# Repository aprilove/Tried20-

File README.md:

# Tried20%

An attempt at creating a 20% mechanical keyboard without an Arduino. 

- [ ] Reroute to remove the amount of vias
- [x] Add circuit protection

A follow up will probably be made to improve the readibility by implementing an Arduino Pro Micro.

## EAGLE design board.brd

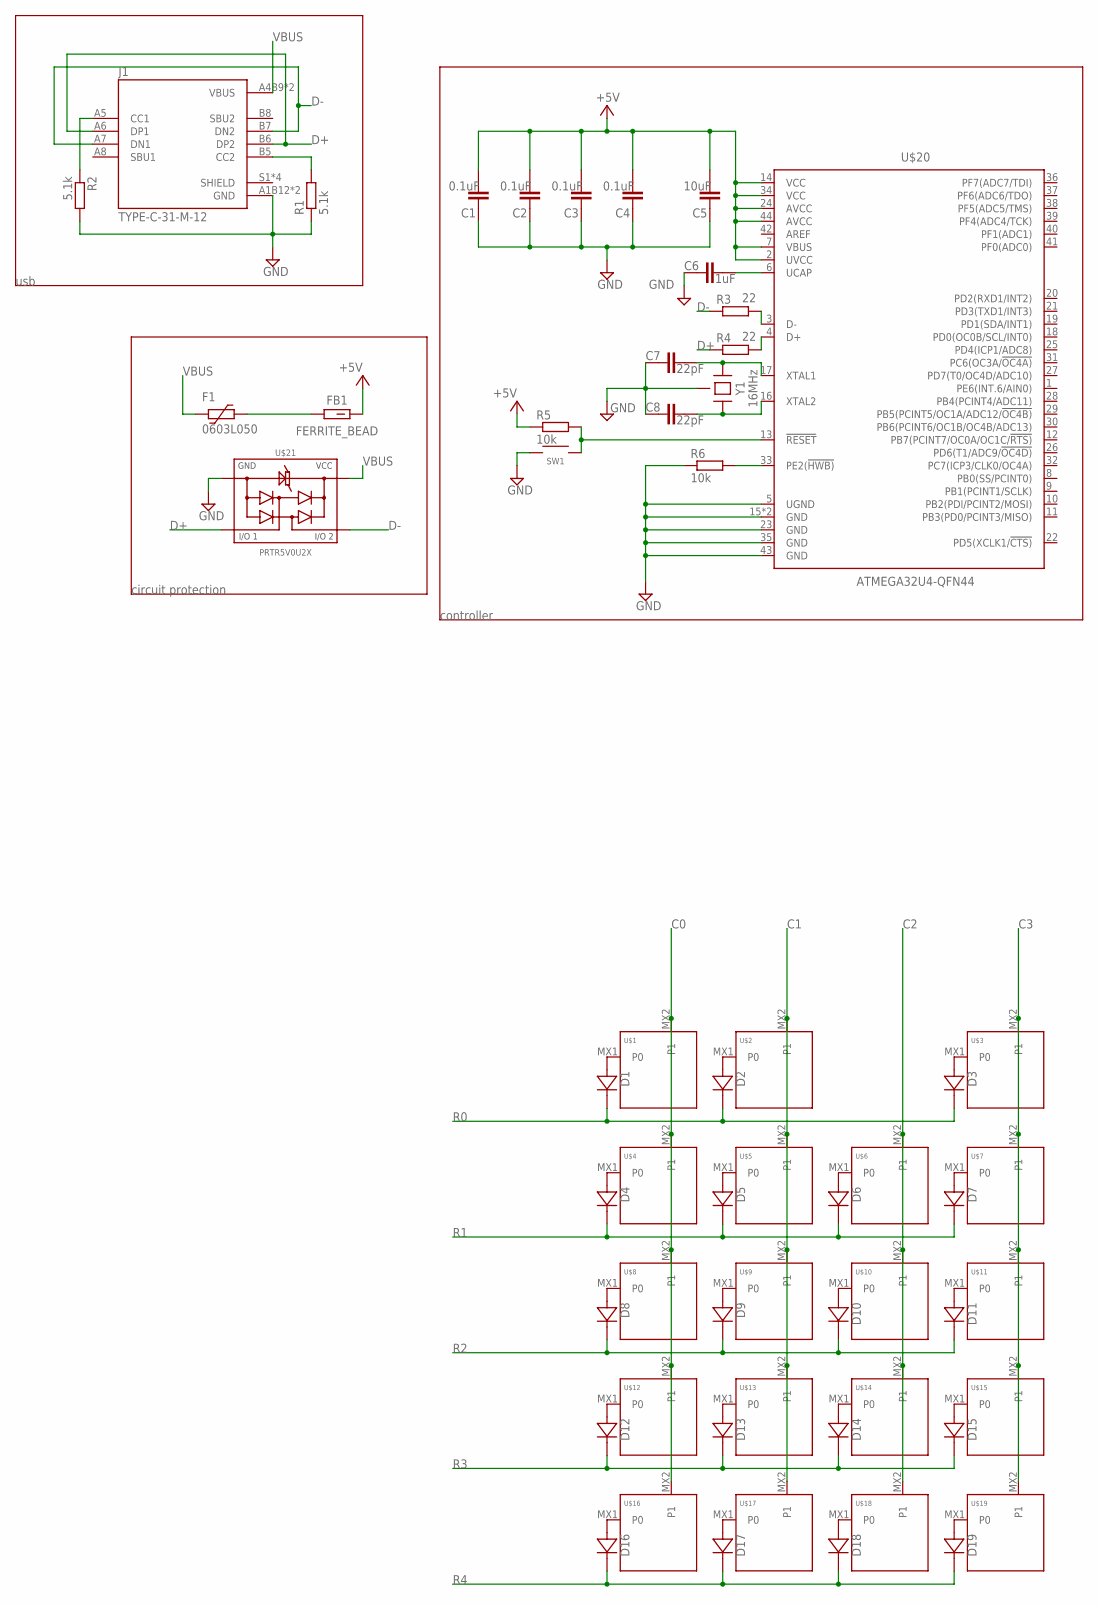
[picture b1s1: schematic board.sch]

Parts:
C1, C2, C3, C4: 0.1uF; C0603
C5: 10uF; C0603
C6: 1uF; C0603
C7, C8: 22pF; C0603
D1, D2, D3, D4, D5, D6, D7, D8, D9, D10, D11, D12, D13, D14, D15, D16, D17, D18, D19: DIODE-SOD-123; SOD-123
F1: 0603L050; 0603L
FB1: FERRITE_BEAD; BEADC1608X95N
J1: TYPE-C-31-M-12; HRO_TYPE-C-31-M-12
R1, R2: 5.1k; R0603
R3, R4: 22; R0603
R5, R6: 10k; R0603
SW1: SWITCH-SMD-EVP-BB2A9B00
U$1, U$3, U$4, U$5, U$6, U$7, U$8, U$9, U$10, U$11, U$12, U$13, U$14, U$15, U$16, U$17, U$18, U$19: KEYSWITCH-PLAIN-MX-1U; MX-1U
U$2: KEYSWITCH-PLAIN-MX-2U-FLIPPED; MX-2U-FLIPPED
U$20: ATMEGA32U4-QFN44; QFN-44
U$21: PRTR5V0U2X
Y1: 16MHz; CRYSTAL-3.2X2.5

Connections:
C0: U$1.MX2 (P1), U$4.MX2 (P1), U$8.MX2 (P1), U$12.MX2 (P1), U$16.MX2 (P1)
C1: U$2.MX2 (P1), U$5.MX2 (P1), U$9.MX2 (P1), U$13.MX2 (P1), U$17.MX2 (P1)
C2: U$6.MX2 (P1), U$10.MX2 (P1), U$14.MX2 (P1), U$18.MX2 (P1)
C3: U$3.MX2 (P1), U$7.MX2 (P1), U$11.MX2 (P1), U$15.MX2 (P1), U$19.MX2 (P1)
D+: J1.A6 (DP1), J1.B6 (DP2), R4.1, U$21.2
D-: J1.A7 (DN1), J1.B7 (DN2), R3.1, U$21.3
GND: C1.1, C2.1, C3.1, C4.1, C5.1, C6.1, C7.1, C8.1, J1.A1B12 (GND), J1.B1A12 (GND), R1.1, R2.2, R6.1, SW1.A@1 (1), SW1.A@2 (1), U$20.5 (UGND), U$20.15 (GND), U$20.23 (GND), U$20.35 (GND), U$20.43 (GND), U$20.TAB (GND), U$21.1, Y1.2 (GND), Y1.4 (GND)
unnamed: D1.A, U$1.MX1 (P0)
unnamed: D2.A, U$2.MX1 (P0)
unnamed: D3.A, U$3.MX1 (P0)
unnamed: D4.A, U$4.MX1 (P0)
unnamed: D5.A, U$5.MX1 (P0)
unnamed: D6.A, U$6.MX1 (P0)
unnamed: D7.A, U$7.MX1 (P0)
unnamed: D8.A, U$8.MX1 (P0)
unnamed: D9.A, U$9.MX1 (P0)
unnamed: D10.A, U$10.MX1 (P0)
unnamed: D11.A, U$11.MX1 (P0)
unnamed: D12.A, U$12.MX1 (P0)
unnamed: D13.A, U$13.MX1 (P0)
unnamed: D14.A, U$14.MX1 (P0)
unnamed: D15.A, U$15.MX1 (P0)
unnamed: D16.A, U$16.MX1 (P0)
unnamed: D17.A, U$17.MX1 (P0)
unnamed: D18.A, U$18.MX1 (P0)
unnamed: D19.A, U$19.MX1 (P0)
unnamed: J1.A5 (CC1), R2.1
unnamed: C6.2, U$20.6 (UCAP)
unnamed: C7.2, U$20.17 (XTAL1), Y1.1
unnamed: J1.B5 (CC2), R1.2
unnamed: R3.2, U$20.3 (D-)
unnamed: R4.2, U$20.4 (D+)
unnamed: C8.2, U$20.16 (XTAL2), Y1.3 (2)
unnamed: R5.2, SW1.B@3 (2), SW1.B@4 (2), U$20.13 (!RESET)
unnamed: R6.2, U$20.33 (PE2(!HWB))
unnamed: F1.1, FB1.1
R0: D1.C, D2.C, D3.C
R1: D4.C, D5.C, D6.C, D7.C
R2: D8.C, D9.C, D10.C, D11.C
R3: D12.C, D13.C, D14.C, D15.C
R4: D16.C, D17.C, D18.C, D19.C
VBUS: F1.2, J1.A4B9 (VBUS), J1.B4A9 (VBUS), U$21.4
VCC: C1.2, C2.2, C3.2, C4.2, C5.2, FB1.2, R5.1, U$20.2 (UVCC), U$20.7 (VBUS), U$20.14 (VCC), U$20.24 (AVCC), U$20.34 (VCC), U$20.44 (AVCC)

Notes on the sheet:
controller
usb
circuit protection

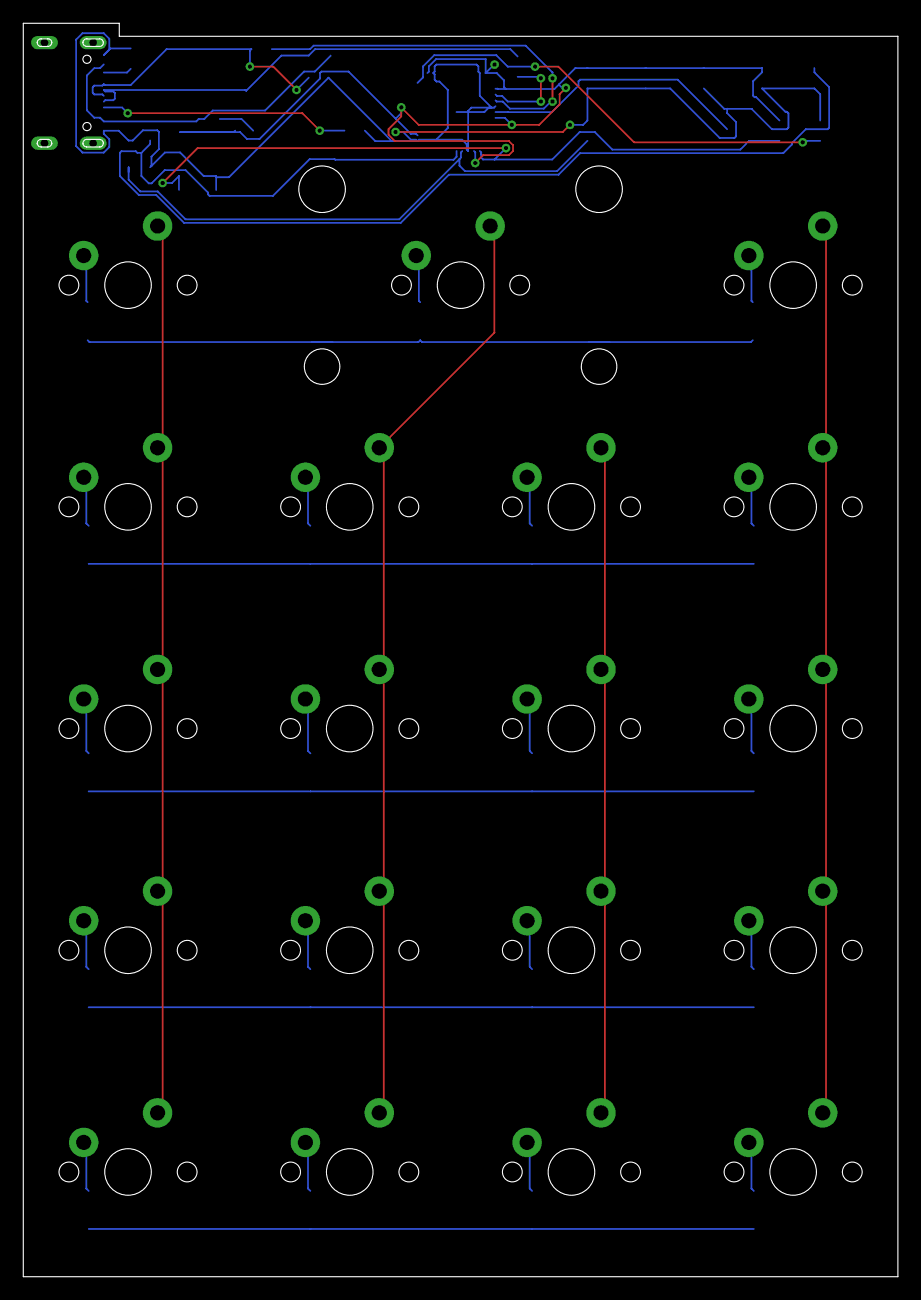
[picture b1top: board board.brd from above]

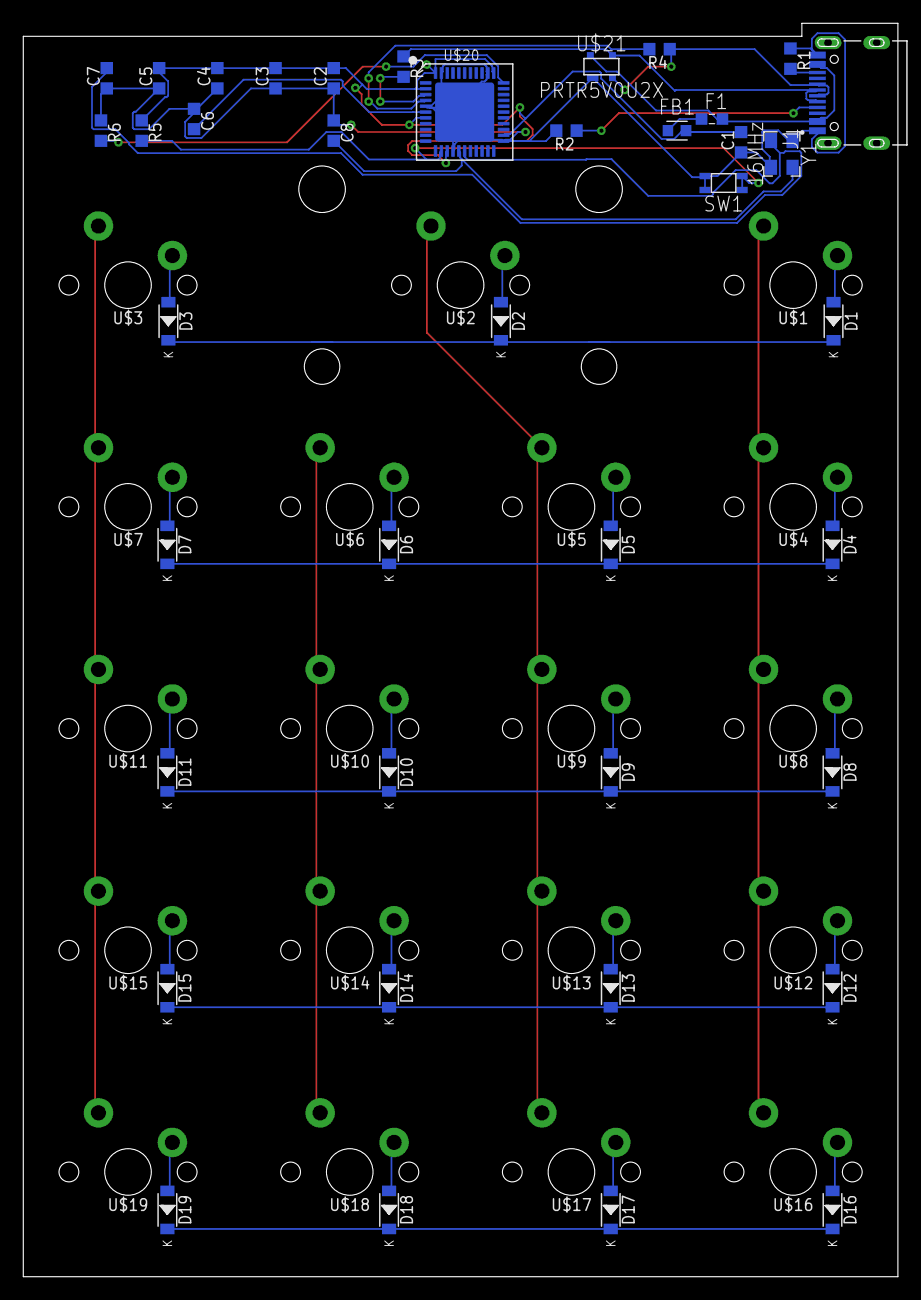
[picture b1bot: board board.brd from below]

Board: 2 copper layers, 75.1 x 107.7 mm, 59 parts (40 on the bottom side), 43 nets.
